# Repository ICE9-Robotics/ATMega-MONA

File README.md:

# ATMega-MONA
Original MONA when it contained an ATMega 328p chip

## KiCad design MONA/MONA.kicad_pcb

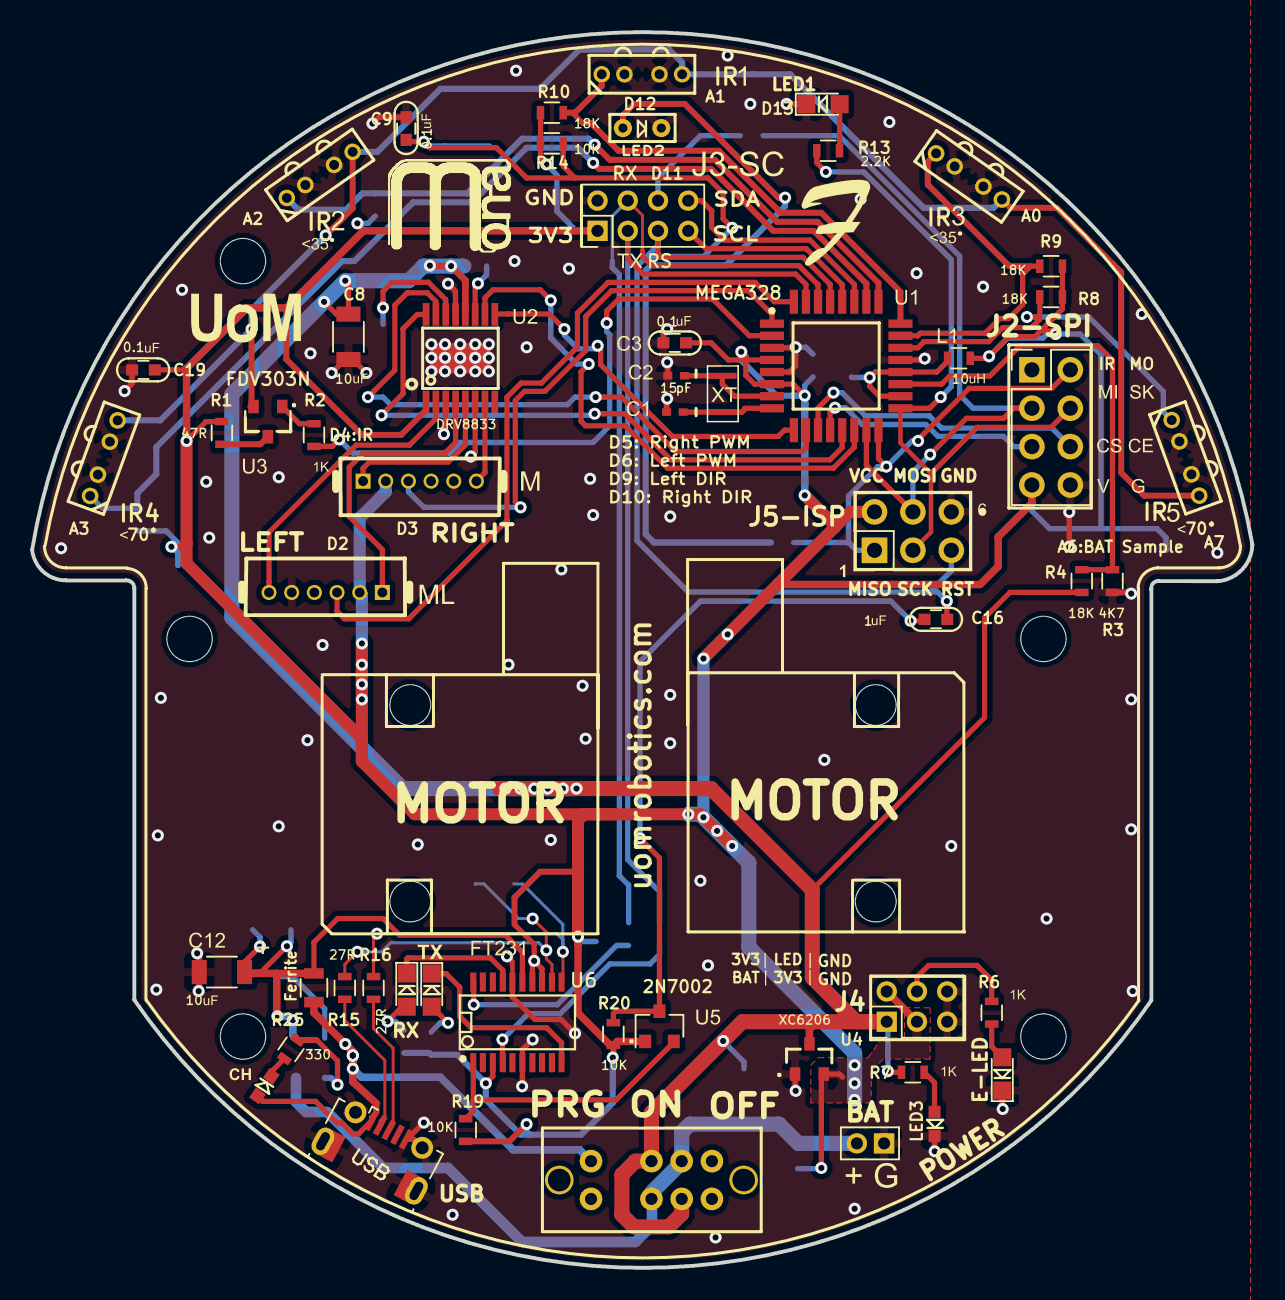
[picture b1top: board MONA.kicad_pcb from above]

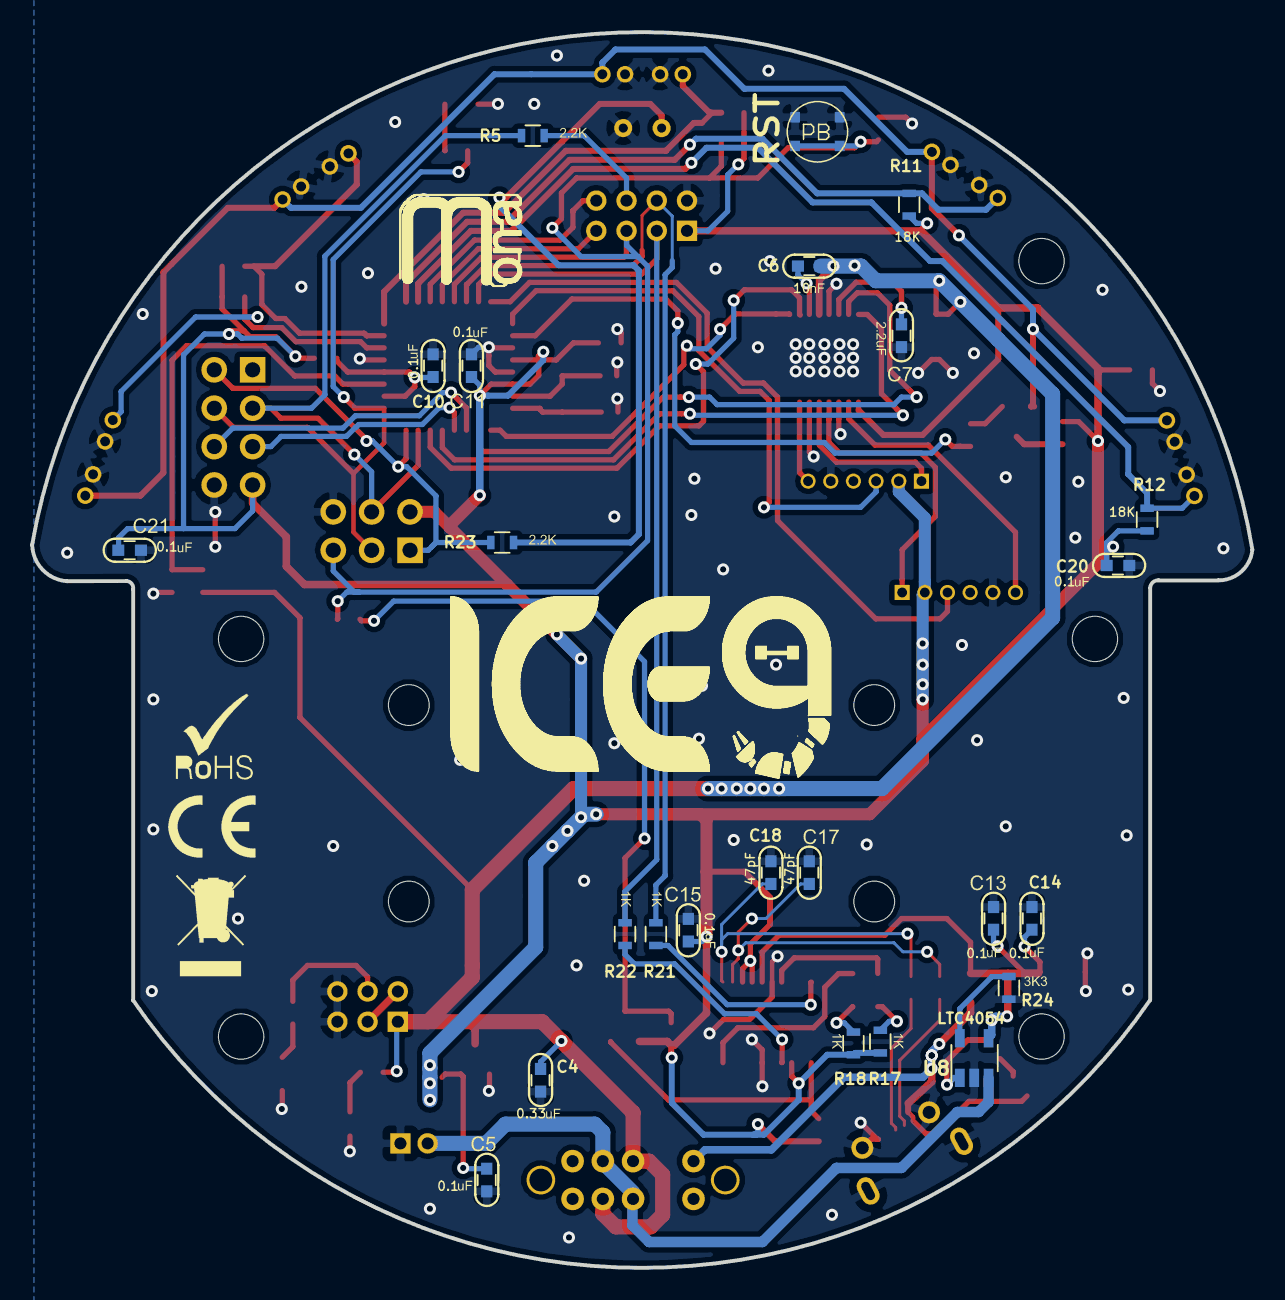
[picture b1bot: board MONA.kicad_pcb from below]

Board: 2 copper layers, 80.7 x 81.8 mm, 87 parts (24 on the bottom side), 62 nets.

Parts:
C1, C2: 15pF , 10V; C_0402_NoSilk
C3, C5, C9, C10, C11, C13, C14, C15, C19, C20, C21: 0.1uF , 10V; C_0603
C4: 0.33uF , 10V; C_0603
C6: 10nF , 10V; C_0603
C7: 2.2uF , 10V; C_0603
C8, C12: 10uF , 10V; C_1206
C16: 1uF , 10V; C_0603
C17, C18: 47pF , 10V; C_0603
CH0: LED; LED_0603
D1, D2: LED; LED_0805
E-LED0: LED; LED_0805
F1: Ferrite_Bead; L_0805
IR1, IR2, IR3, IR4, IR5: TCRT1000
J1: Conn_01x02 1.8mm pitch; BAT_conn_1x02_Pitch1.8mm
J2: HEADER 02x04 2.54mm; Pin_Header_Straight_2x04_Pitch2.54mm
J3: HEADER 02x04 2mm; Pin_Header_Straight_2x04_Pitch2.00mm
J4: HEADER 02x03 2mm; Pin_Header_Straight_2x03_Pitch2.00mm
J5: HEADER 02x03 2.54mm; Pin_Header_Straight_2x03_Pitch2.54mm
L1: 10uH; L_0603
LED3: LED; LED_0603
M1, M2, M3, M4, M5: Mounting_Hole; MountingHole_3mm
M6, M7, M8, M9: Mounting_Hole; MountingHole_2.7mm_M2.5
ML1: Motor connector 01x06 1.5mm; Pin_Header_Straight_1x06_Pitch1.27mm
MR1: Motor connector 01x06 1.5mm; Pin_Header_Straight_1x06_Pitch1.27mm
PB0: SW_Push; KMT221NGHFLFS
R1: 47R; R_0603
R2, R6, R7, R17, R18, R21, R22: 1K; R_0603
R3: 4.7K; R_0603
R4, R8, R9, R10, R11, R12: 18K; R_0603
R5, R13, R23: 2.2K; R_0603
R14, R19, R20: 10K; R_0603
R15, R16: 27R; R_0603
R24: 3.3K; R_0603
R25: 330R; R_0603
RX_LED1: LED; LED_0805
SW1: OS203011MA2QP1
TX_LED1: LED; LED_0805
U1: ATMEGA328P-AU; TQFP-32_7x7mm_Pitch0.8mm
U2: DRV8833; HTSSOP-16
U3: FDV303N; SOT-23
U4: XC6206; SOT-23
U5: 2N7002; SOT-23
U6: FT231XS; SSOP-20
U8: LTC4054ES5-4.2; TSOT-23-5
USB0: USB_OTG; USB_Micro-B_Molex-105017-0001
XT1: Crystal_Small; CSTCE

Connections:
+3V3: C3.2, C5.2, C11.1, C15.2, C19.2, C20.2, C21.2, J2.7, J3.1, J4.2, J4.3, J5.2, L1.1, ML1.2, MR1.2, R1.1, R8.2, R9.2, R10.2, R11.2, R12.2, R14.2, R17.2, R18.2, R19.2, R20.2, U1.4, U1.6, U2.1, U4.2, U5.1, U6.3, U6.13, U6.14
+BATT: C4.2, C6.2, C8.1, J4.1, R4.2, R7.1, SW1.2, SW1.7, U2.12, U4.3
/AD0: IR3.4, R9.1, U1.23
/AD1: IR1.4, R10.1, U1.24
/AD2: IR2.4, R11.1, U1.25
/AD3: IR4.4, R12.1, U1.26
/ADC6: R3.2, R4.1, U1.19
/ADC7: IR5.4, R8.1, U1.22
/C2_L: ML1.3, U1.32
/C2_R: MR1.3, U1.1
/CHRG: R25.2, U8.1
/D4: R2.2, U1.2
/D5: U1.9, U2.9
/D6: U1.10, U2.15
/D7: J2.6, U1.11
/D8: J2.5, U1.12
/D9: U1.13, U2.16
/D10: U1.14, U2.10
/D11: J3.6, R5.1
/D11_MOSI: J2.3, J5.4, R5.2, U1.15
/D12_MISO: J2.2, J5.1, R23.1, U1.16
/D13_SCK: J2.4, J5.3, R13.1, U1.17
/D+: R16.1, USB0.3
/D-: R15.1, USB0.2
/IR_PWR: IR1.1, IR2.1, IR3.1, IR4.1, IR5.1, U3.2
/LED_E: J4.4, R6.1
/M1_L: ML1.6, U2.2
/M1_R: MR1.6, U2.7
/M2_L: ML1.1, U2.4
/M2_R: MR1.1, U2.5
/RAW_BATT: J1.2, SW1.3, SW1.6, U8.3
/RS: C9.2, C16.2, J3.5, J5.5, PB0.2, R14.1, U1.29
/RX: J3.4, R21.1, U1.30
/SCL: J3.7, U1.28
/SDA: J3.8, U1.27
/TX: J3.3, R22.1, U1.31
/VBUS: CH0.2, F1.2, SW1.1, USB0.1
/VBUS_FIL: C12.2, C13.2, C14.2, F1.1, U6.15, U8.4
/~DTR: R19.1, U5.2, U6.1
GND: C1.2, C2.2, C3.1, C4.1, C5.1, C7.1, C8.2, C9.1, C10.2, C11.2, C12.1, C13.1, C14.1, C15.1, C17.2, C18.1, C19.1, C20.1, C21.1, D1.1, D2.1, E-LED0.1, IR1.2, IR1.3, IR2.2, IR2.3, IR3.2, IR3.3, IR4.2, IR4.3, IR5.2, IR5.3, J1.1, J2.8, J3.2, J4.5, J4.6, J5.6, LED3.1, ML1.5, MR1.5, PB0.1, R3.1, R24.1, U1.3, U1.5, U1.21, U2.3, U2.6, U2.13, U4.1, U6.6, U6.16, U8.2, USB0.5, USB0.6
unnamed: C1.1, U1.8, XT1.2
unnamed: C2.1, U1.7, XT1.1
unnamed: C6.1, U2.11
unnamed: C7.2, U2.14
unnamed: C10.1, L1.2, U1.18, U1.20
unnamed: C16.1, R20.1, U5.3
unnamed: C17.1, R15.2, U6.12
unnamed: C18.2, R16.2, U6.11
unnamed: CH0.1, R25.1
unnamed: D1.2, R13.2
unnamed: D2.2, R23.2
unnamed: E-LED0.2, R6.2
unnamed: LED3.2, R7.2
unnamed: R1.2, U3.3
unnamed: R2.1, U3.1
unnamed: R17.1, RX_LED1.2
unnamed: R18.1, TX_LED1.2
unnamed: R21.2, U6.20
unnamed: R22.2, U6.4
unnamed: R24.2, U8.5
unnamed: RX_LED1.1, U6.17
unnamed: TX_LED1.1, U6.10

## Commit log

2023-02-08 First upload
    It's a bit messy, will need to clear it up!
